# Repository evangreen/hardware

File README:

USBtiny
=======

USBtiny is a software implementation of the USB low-speed protocol for
the Atmel ATtiny microcontrollers. Of course, it will also work on the
ATmega series. The software is written for an AVR clocked at 12 MHz.
At this frequency, each bit on the USB bus takes 8 clock cycles, and
with a lot of trickery, it is possible to decode and encode the USB
waveforms by software. The USB driver needs between 1300 and 1400
bytes of flash space (excluding the optional identification strings),
depending on the configuration and compiler version, and 46 bytes RAM
(excluding stack space). The C interface consists of 3 to 5 functions,
depending on the configuration.

Implementation
==============

USB uses two differential data signals, D+ and D-, which are normally
complementary. However, the end of a packet is signalled by pulling
both signals low. Data is not transmitted directly on the USB bus, it
is NRZI encoded first. This means that a "0" bit is encoded as a bit
change, and a "1" bit is encoded as no bit change. After 6 "1" bits,
"bit stuffing" takes place to force a change on the USB signal lines.

The software is interrupt driven: the start of a USB packet triggers
an interrupt. The interrupt handler synchronizes with the sync byte,
removes the NRZI encoding and bit stuffing, and stores the packed in
one of the two RAM buffers. Two buffers are used so that the next
packet can be received while the current one is being processed.
Depending on the packet type, a reply packed may be sent back
immediately in the interrupt handler.

The rest of the USB driver is written in C. A usb_poll() function
must to be called periodically to poll for incoming packets. Only a
single endpoint is supported at the moment. Standard control requests
are directly handled by the USB driver. Other SETUP requests are
forwarded to a user-supplied function usb_setup(). Support for large
replies and OUT control requests is optional, see usbtiny.h.

To use the USB driver in your own application, you need to configure
the macros in usbtiny.h, and provide a function usb_setup() to handle
SETUP control packets. Optionally, you need to provide the functions
usb_in() and usb_out(). Your code needs to call the initialization
function usb_init() at program startup, and usb_poll() at regular
intervals. The AVR device type and the upload command should be
configured at the top of the Makefile.

Other USB projects
==================

This software was inspired by two similar USB projects for the AVR:

  http://www.cesko.host.sk/IgorPlugUSB/IgorPlug-USB%20(AVR)_eng.htm
  http://www.obdev.at/products/avrusb/index.html

My version has the advantage that you have more freedom over which I/O
pins to use for the D+ and D- USB signals. You don't need to use bit 0
for the D+ signal. The only restriction is that both signals should be
on the same I/O port. When you select a pin for D+ that can also
generate an interrupt, only two I/O pins are required. The pin-change
interrupt is deliberately not used, so that it remains available for
other uses.

Another improvement is that the CRC calculation is faster, because it
uses a lookup table. A bit-wise calculation turned out to be too slow
for the USB controller in my laptop. For instance, the obdev code
worked fine on my desktop computer, but not on my laptop.

Apart from these advantages, I think that my code is more readable and
easier to configure, but that impression may be caused by a mild form
of the NIH syndrome that I'm suffering from. In any case, I learned a
lot about the USB protocol, and writing the interrupt handler was a
nice puzzle.

Hardware
========

The AVR must be clocked with an external 12 MHz crystal. For an
ATtiny2313, this means that the low fuse byte must be reprogrammed,
for instance to 0xff. I also recommend to enable the BOD circuit,
when available. For the ATtiny2313, this means programming the high
fuse byte to 0xdb (BOD level is 2.7V).

The USB data signals are specified at 3.3V. The easiest way to
accomplish this is to use a 3.3V power supply for the AVR. However,
driving the USB signals with 5V seems to work as well in most cases,
which may be more convenient when you need to interface to 5V
peripherals. According to the USB specification, a device should not
be damaged by 5V signals. I've been running the AVR and USB bus at 5V,
and haven't encounter any problems so far, but I have some reports
of Viao laptops that do not work with 5V signals. In that case, you
can reduce the voltage of the USB data signals by adding 3V6 zener
diodes from the data signals to ground.

USBtiny SPI converter
=====================

My first USBtiny application is a USB to SPI (Serial Programming
Interface) converter. The SPI signals are connected to a female DB-25
connecter, so that the converter can be plugged onto my AVR parallel
port programmer. Because the most important parallel port signals are
connected to the DB-25 connecter, the same hardware (with different
firmware) could be used to control other parallel port devices. That
is also the reason why I connected the ACK signal to the INT1 pin.
I didn't bother to put capacitors on the crystal, but they are
recommended for reliable operation. The software, the schematic and
a Python test script can be found in the "spi" subdirectory.

The circuit may be powered via the diode at pin 14 of the DB-25
connector to enable reprograming the ATtiny2313 in-system. This
requires an adaptor cable between another SPI programmer and a DB-25
male connector with the following connections:

  SPI  DB25
  ---  ----
  GND    25
  VCC    14
  RESET  13
  SCK     9
  MISO    8
  MOSI    7

Bit-banging the SPI signals via USB turned out to be very slow. To get
reasonable programming speeds, I've moved the SPI algorithm into the
AVR. This means that you can send a 32-bit SPI command in a single USB
packet. In addition, you can read or write up to 255 bytes from/to
flash or EEPROM in a single control transfer.

The subdirectory "patches" contains a patch for avrdude-5.1 that adds
support for controlling this SPI converter. The programmer name is
"usbtiny". You can use the -B option or the "sck" command to specify
the minimum SCK period in microseconds (range: 1..250, default: 10).

USBtiny LIRC compatible IR receiver and LCD controller
======================================================

A second USBtiny application is a receiver for infrared remote
controls that can be used with the LIRC package (http://www.lirc.org/).
The firmware stores the mark/space timings from a TSOP1738 IR decoder
in a buffer that is polled by a LIRC device driver. As a visual
feedback, a LED is flashed when a signal is being received. As an
additional (optional) feature, a 2x16 LCD display is attached to PORTB.
You can control the display via the USB bus. The software, the schematic
and a Python test script can be found in the "ir" subdirectory.
A pull-down resistor at PB3 prevents a hang in the LCD initialization
code when no LCD is attached to PORTB. You can disable the LCD code by
setting the LCD_PRESENT macro in main.c to 0.

I adopted the "IgorPlug-USB" protocol, so that the existing LIRC
device driver "igorplugusb" could be used without modifications.
Nevertheless, a patch for lirc-0.8.0 is included in the "patches"
subdirectory, with the following modifications:
1) An increase of the sample rate from 10 to 100 times per second.
   This is not required, but improves the responsiveness and repeat
   behavior for some remote controls.
2) A fix from Reinhard Max to get correct gap timings.
3) A compilation fix for the latest 2.6 Linux kernels.

Tools
=====

The software was developed on a Linux system. In addition to standard
tools like GNU make, you need the AVR versions of gcc, binutils and
glibc to build the code: On a Debian/Ubuntu system, you can apt-get
the following packages:

  gcc-avr
  binutils-avr
  avr-libc

To upload the code to an AVR, I use avrdude with a parallel port
programmer.

I initially used gcc-3.4.3 with the -Os option, which generates
reasonable compact code. Unfortunately, newer versions like gcc-4.1.0
generate about 10% more code, and as a result, the application code
did not fit in 2K anymore. To make it fit, I had to remove the optional
vendor and device strings, by undefining the USBTINY_VENDOR_NAME and
USBTINY_DEVICE_NAME macros.

The schematics were created with gschem, which is part of the gEDA
package. The conversion to Postscript is done with a script that
invokes gschem non-interactively.

The "util" and application code subdirectories each contain their own
Makefile. In addition, there is a global Makefile that recursively
invokes all other Makefiles.

Host software
=============

The subdirectory "utils" contains a Python module "usbtiny.py" that
defines a class USBtiny that can be used to communicate with the
USBtiny firmware. This class is used by the test scripts.

The usbtiny.py module uses a Python wrapper around libusb that is
generated by "swig". Type "make" to build the wrapper. Of course, you
need to have swig, libusb and libusb-dev installed on your system.

Libusb needs appropriate permissions to open a USB device. This means
that you either have to run the scripts as "root", or you should
configure the hotplug or udev system to relax the permissions of the
device file created under /proc/bus/usb/ when the device is plugged
in. With udev, you can change the permissions by adding a rule like

  SUBSYSTEM=="usb_device", MODE="0666"

to the udev rules in /etc/udev/rules.d/

License
=======

The USBtiny software is licensed under the terms of the GNU General
Public License as published by the Free Software Foundation, either
version 2 of the license, or (at your option) any later version. A
copy of the GPL version 2 license can be found in the file COPYING.

Author & website
================

Dick Streefland <dick@streefland.net>

http://www.google.com/search?btnI&q=webtag_net_streefland_avr_usbtiny

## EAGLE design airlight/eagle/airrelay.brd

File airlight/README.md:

# Airlight

Airlight was a set of two hardware boards I started in 2013 in order to control the traffic lights I've collected in my house. It was also my first foray into the world of Wireless with the RFM22B boards.

### Design

The system consists of two components: a master board and several identical relay boards (one in each traffic light).

The master board is the brains behind the system. It contains the traffic controller logic, and sends out wireless commands to the relay boards in the traffic lights. The controller logic is an 8-phase semi-actuated traffic controller based on my previous work in college studying an old Crouse Hinds DM-800 controller. There are only enough LEDs to display 4 phases at once, but the controller logic can technically run 8 phases plus 4 overlap lights. This is equivalent to a 4 way intersection with protected lefts and protected rights in each direction. The traffic controller part also compiles for Windows so that I can test the traffic control sequencing without burning new firmware.

The relay boards are nearly stateless. They have a phase ID and pedestrian boolean burned uniquely into the firmware of each board so that each light knows which phase to respond to. They listen for wireless commands and respond appropriately. I also programmed in an RSSI response mode in case I needed to debug signal quality issues.

The relay board receives commands via the RFM22B wireless board into an ATMega168 MCU. It listens to incoming wireless messages corresponding to its phase and ped ID, and updates its 3 output pins (red, yellow, and green). The output pins are connected via optoisolators to triacs, which can flip 120VAC line voltage on or off.

### Results

Overall the project went very well. I was very pleased with the signal strength of the RFM22B boards. Reception was great anywhere in my admittedly tiny apartment, even though the relay boards were buried inside metal traffic lights. There are a couple of board errata, which were easy enough to fix and should be documented.

One aspect that I'm less than pleased about is the sharing of the SPI bus between the RFM22B and the LEDs on the master board. The RFM22B is very slow to respond, and hogs the bus for long delay periods, meaning every time a wireless command is sent there is visible flickering in the LEDs. If I had known the RFM22B was going to be a so slow I would have wired the LEDs separately, or maybe used something like an HT16K33 to drive the LEDs.

### Pictures
Some photos of the lights in my apartment

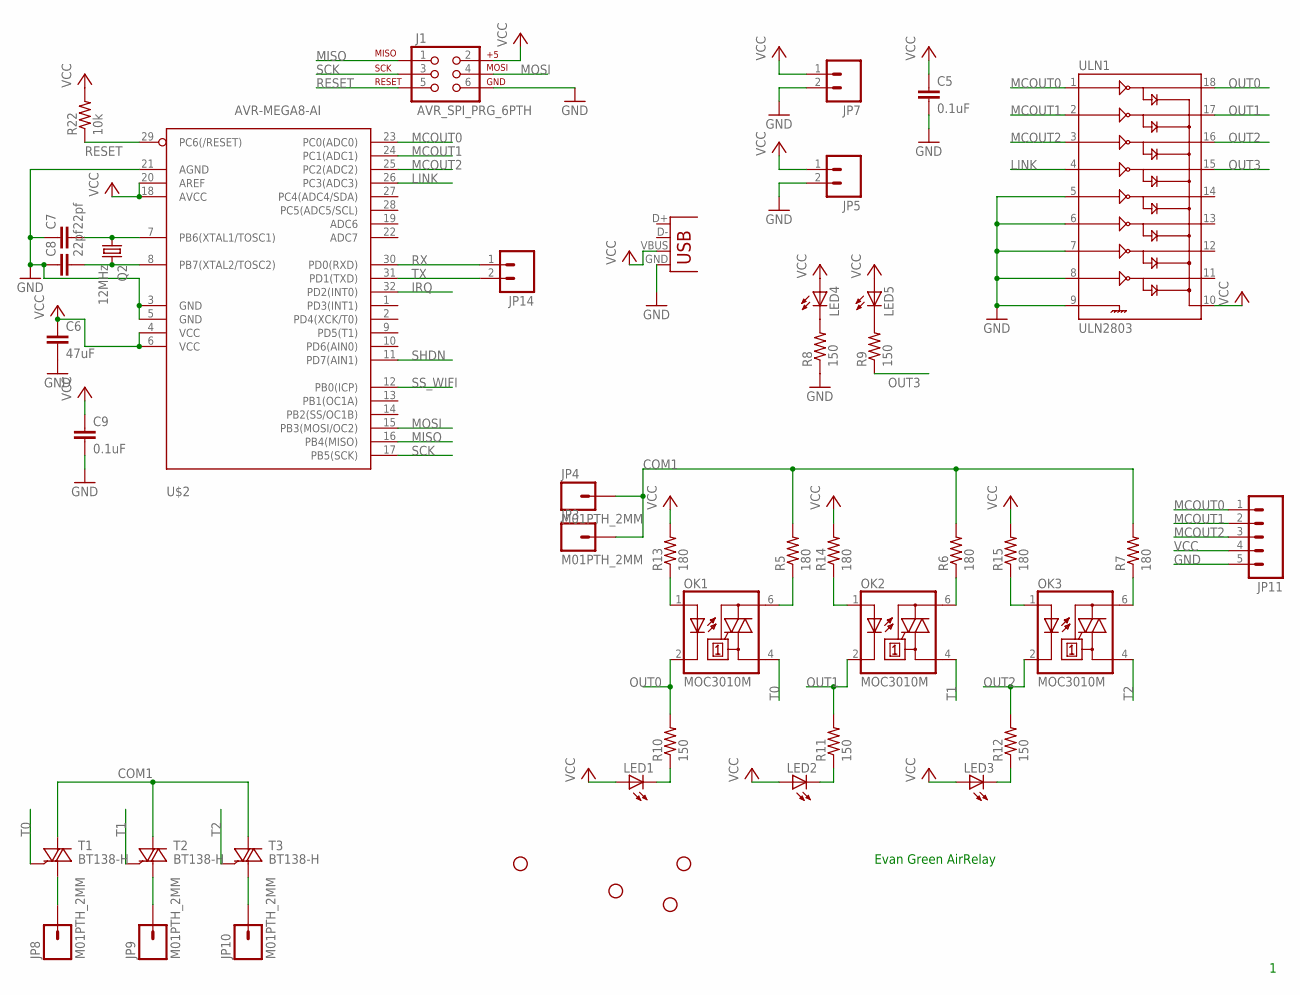
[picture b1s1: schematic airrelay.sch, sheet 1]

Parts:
C5, C9: 0.1uF; 0402-CAP
C6: 47uF; 1210
C7, C8: 22pf; 0402-CAP
J1: AVR_SPI_PRG_6PTH; 2X3
JP2, JP6, JP12, JP13: STAND-OFF
JP3, JP4, JP8, JP9, JP10: M01PTH_2MM; 1X01_2MM
JP5, JP7, JP14: M02PTH; 1X02
JP11: M05PTH; 1X05
LED1, LED2, LED3: LED5MM
LED4, LED5: LED3MM
OK1, OK2, OK3: MOC3010M; DIL06
Q2: 12MHz; TC38H
R5, R6, R7: 180; AXIAL-0.4
R8, R9, R10, R11, R12: 150; 0402-RES
R13, R14, R15: 180; 0402-RES
R22: 10k; 0402-RES
T1, T2, T3: BT138-H; TO220BH
U$2: AVR-MEGA8-AI; TQFP32-08
ULN1: ULN2803; SO18L
X1: USBSMD; USB-MINIB

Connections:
COM1: JP3.1, JP4.1, R5.P$2 (2), R6.P$2 (2), R7.P$2 (2), T1.T2 (A2), T2.T2 (A2), T3.T2 (A2)
GND: C5.2, C6.2, C7.1, C8.1, C9.2, J1.6, JP5.2, JP7.2, JP11.5, R8.1, U$2.3 (GND), U$2.5 (GND), U$2.21 (AGND), ULN1.5, ULN1.6, ULN1.7, ULN1.8, ULN1.9, X1.GND; also elsewhere on the board
IRQ: U$2.32 (PD2(INT0)); also elsewhere on the board
LINK: U$2.26 (PC3(ADC3)), ULN1.4
MCOUT0: JP11.1, U$2.23 (PC0(ADC0)), ULN1.1
MCOUT1: JP11.2, U$2.24 (PC1(ADC1)), ULN1.2
MCOUT2: JP11.3, U$2.25 (PC2(ADC2)), ULN1.3
MISO: J1.1, U$2.16 (PB4(MISO))
MOSI: J1.4, U$2.15 (PB3(MOSI/OC2)); also elsewhere on the board
unnamed: OK1.1 (A), R13.1
unnamed: OK2.1 (A), R14.1
unnamed: OK3.1 (A), R15.1
unnamed: LED4.K (C), R8.2
unnamed: LED5.K (C), R9.2
unnamed: LED3.K (C), R12.1
unnamed: OK1.6 (A2), R5.P$1 (1)
unnamed: OK2.6 (A2), R6.P$1 (1)
unnamed: OK3.6 (A2), R7.P$1 (1)
unnamed: LED2.K (C), R11.1
unnamed: LED1.K (C), R10.1
unnamed: C7.2, Q2.1, U$2.7 (PB6(XTAL1/TOSC1))
unnamed: JP8.1, T1.T1 (A1)
unnamed: JP9.1, T2.T1 (A1)
unnamed: JP10.1, T3.T1 (A1)
unnamed: C8.2, Q2.2, U$2.8 (PB7(XTAL2/TOSC2))
OUT0: OK1.2 (C), R10.2, ULN1.18
OUT1: OK2.2 (C), R11.2, ULN1.17
OUT2: OK3.2 (C), R12.2, ULN1.16
OUT3: R9.1, ULN1.15
RESET: J1.5, R22.1, U$2.29 (PC6(/RESET))
RX: JP14.1, U$2.30 (PD0(RXD))
SCK: J1.3, U$2.17 (PB5(SCK)); also elsewhere on the board
SHDN: U$2.11 (PD7(AIN1)); also elsewhere on the board
SS_WIFI: U$2.12 (PB0(ICP)); also elsewhere on the board
T0: OK1.4 (A1), T1.G
T1: OK2.4 (A1), T2.G
T2: OK3.4 (A1), T3.G
TX: JP14.2, U$2.31 (PD1(TXD))
VCC: C5.1, C6.1, C9.1, J1.2, JP5.1, JP7.1, JP11.4, LED1.A, LED2.A, LED3.A, LED4.A, LED5.A, R13.2, R14.2, R15.2, R22.2, U$2.4 (VCC), U$2.6 (VCC), U$2.18 (AVCC), U$2.20 (AREF), ULN1.10, X1.VBUS

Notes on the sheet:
Evan Green AirRelay

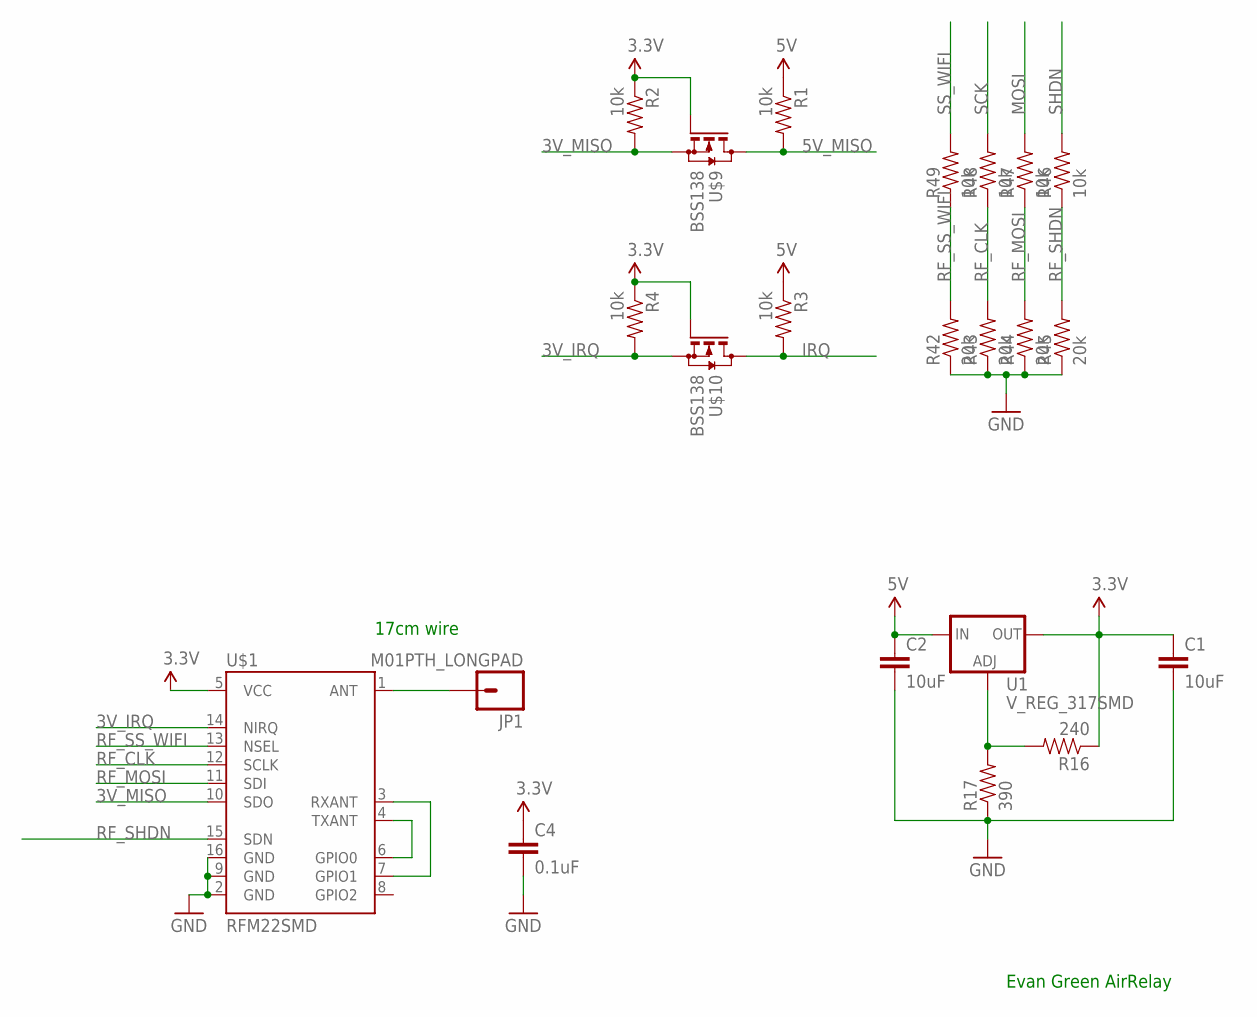
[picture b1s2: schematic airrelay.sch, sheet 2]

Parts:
C1, C2: 10uF; 0805
C4: 0.1uF; 0402-CAP
JP1: M01PTH_LONGPAD; 1X01_LONGPAD
R1, R2, R3, R4, R46, R47, R48, R49: 10k; 0402-RES
R16: 240; 0402-RES
R17: 390; 0402-RES
R42, R43, R44, R45: 20k; 0402-RES
U1: V_REG_317SMD; SOT223
U$1: RFM22SMD; RFM22-XXX-S2
U$9, U$10: BSS138; SOT-323

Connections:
3.3V: C1.1, C4.1, R2.1, R4.1, R16.1, U1.2 (OUT), U$1.5 (VCC), U$9.1 (G), U$10.1 (G)
3V_IRQ: R4.2, U$1.14 (NIRQ), U$10.2 (S)
3V_MISO: R2.2, U$1.10 (SDO), U$9.2 (S)
5V: C2.1, R1.1, R3.1, U1.3 (IN)
5V_MISO: R1.2, U$9.3 (D)
GND: C1.2, C2.2, C4.2, R17.1, R42.1, R43.1, R44.1, R45.1, U$1.2 (GND), U$1.9 (GND), U$1.16 (GND); also elsewhere on the board
IRQ: R3.2, U$10.3 (D); also elsewhere on the board
MOSI: R47.2; also elsewhere on the board
unnamed: R16.2, R17.2, U1.1 (ADJ)
unnamed: U$1.4 (TXANT), U$1.6 (GPIO0)
unnamed: JP1.1, U$1.1 (ANT)
unnamed: U$1.3 (RXANT), U$1.7 (GPIO1)
RF_CLK: R43.2, R48.1, U$1.12 (SCLK)
RF_MOSI: R44.2, R47.1, U$1.11 (SDI)
RF_SHDN: R45.2, R46.1, U$1.15 (SDN)
RF_SS_WIFI: R42.2, R49.1, U$1.13 (NSEL)
SCK: R48.2; also elsewhere on the board
SHDN: R46.2; also elsewhere on the board
SS_WIFI: R49.2; also elsewhere on the board

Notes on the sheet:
Evan Green AirRelay
17cm wire

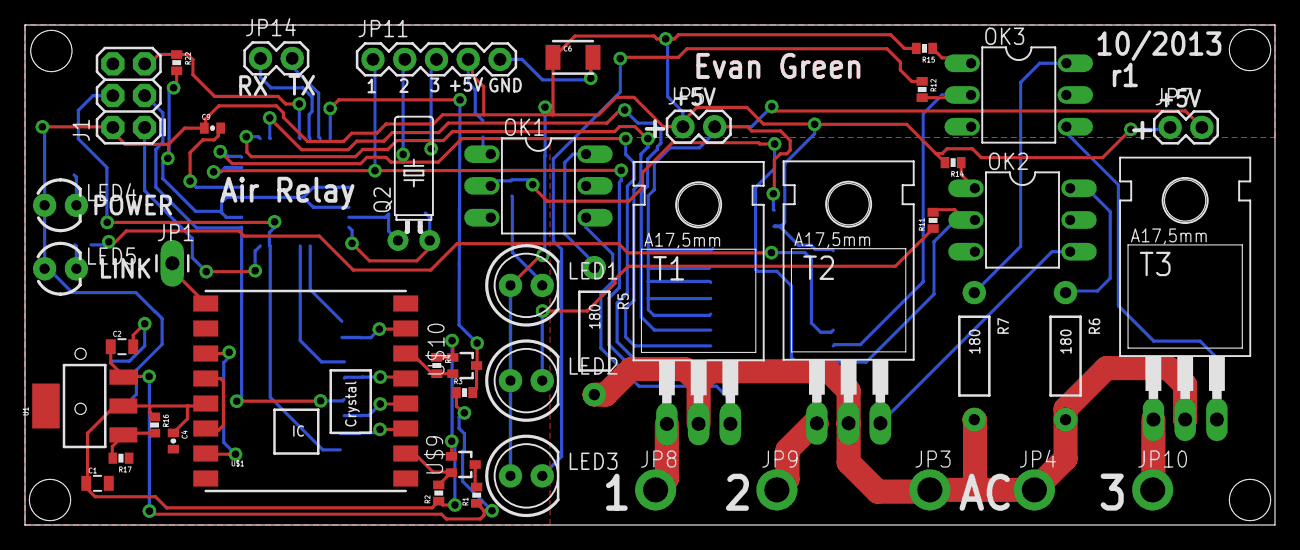
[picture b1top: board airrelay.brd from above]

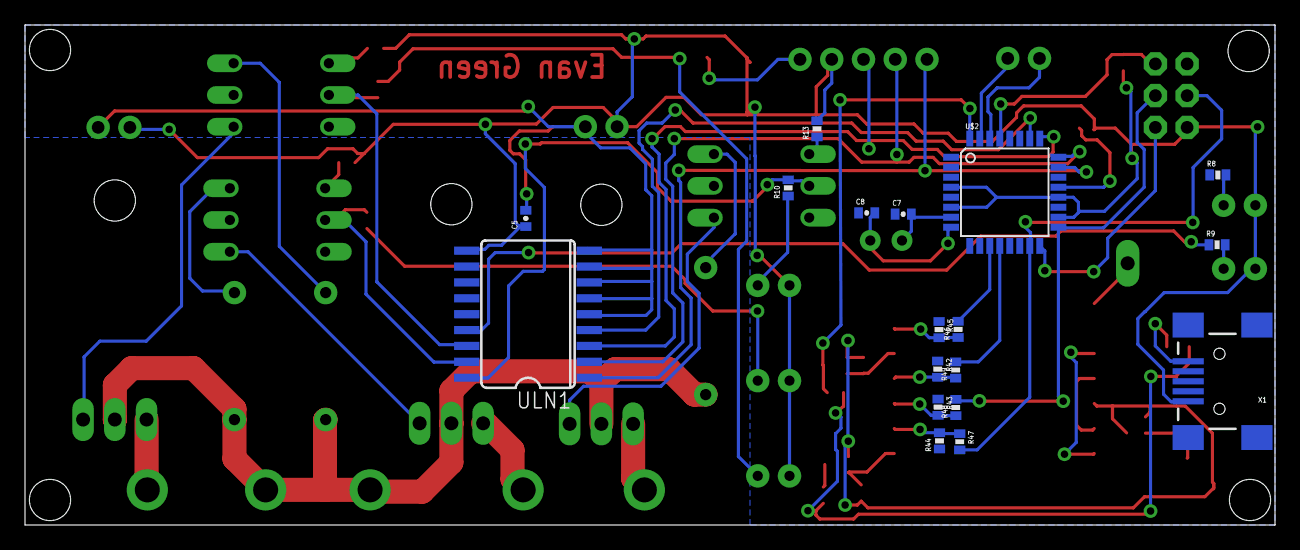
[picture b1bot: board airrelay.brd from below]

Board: 2 copper layers, 100.0 x 40.0 mm, 68 parts (18 on the bottom side), 52 nets.

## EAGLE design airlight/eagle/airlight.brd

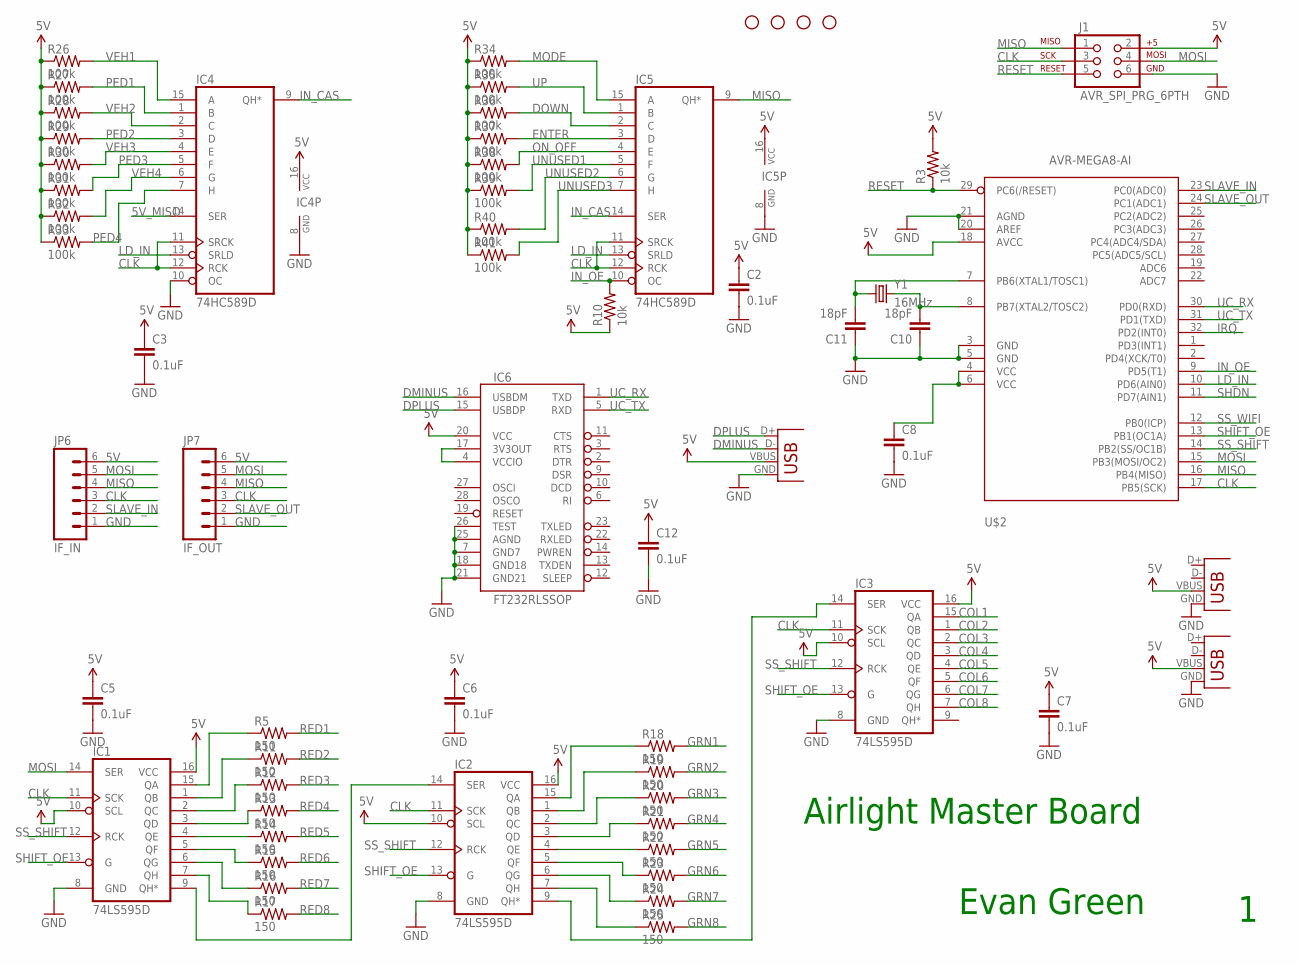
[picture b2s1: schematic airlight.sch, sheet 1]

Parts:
C2, C3, C5, C6, C7, C8, C12: 0.1uF; 0402-CAP
C10, C11: 18pF; 0402-CAP
IC1, IC2, IC3: 74LS595D; SO16
IC4, IC5: 74HC589D; SO16
IC6: FT232RLSSOP; SSOP28DB
J1: AVR_SPI_PRG_6PTH; 2X3
JP2, JP3, JP4, JP5: STAND-OFF
JP6: IF_IN; 1X06
JP7: IF_OUT; 1X06
R3, R10: 10k; 0402-RES
R5, R11, R12, R13, R14, R15, R16, R17, R18, R19, R20, R21, R22, R23, R24, R25: 150; 0402-RES
R26, R27, R28, R29, R30, R31, R32, R33, R34, R35, R36, R37, R38, R39, R40, R41: 100k; 0402-RES
U$2: AVR-MEGA8-AI; TQFP32-08
X1, X2, X3: USBSMD; USB-MINIB
Y1: 16MHz; HC49US

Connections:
5V: C2.1, C3.1, C5.1, C6.1, C7.1, C12.1, IC1.10 (SCL), IC1.16 (VCC), IC2.10 (SCL), IC2.16 (VCC), IC3.10 (SCL), IC3.16 (VCC), IC4.16 (VCC), IC5.16 (VCC), IC6.20 (VCC), J1.2, JP6.6, JP7.6, R3.2, R10.1, R26.1, R27.1, R28.1, R29.1, R30.1, R31.1, R32.1, R33.1, R34.1, R35.1, R36.1, R37.1, R38.1, R39.1, R40.1, R41.1, U$2.18 (AVCC), X1.VBUS, X2.VBUS, X3.VBUS; also elsewhere on the board
5V_MISO: IC4.14 (SER); also elsewhere on the board
CLK: IC1.11 (SCK), IC2.11 (SCK), IC3.11 (SCK), IC4.11 (SRCK), IC4.12 (RCK), IC5.11 (SRCK), IC5.12 (RCK), J1.3, JP6.3, JP7.3, U$2.17 (PB5(SCK)); also elsewhere on the board
COL1: IC3.15 (QA); also elsewhere on the board
COL2: IC3.1 (QB); also elsewhere on the board
COL3: IC3.2 (QC); also elsewhere on the board
COL4: IC3.3 (QD); also elsewhere on the board
COL5: IC3.4 (QE); also elsewhere on the board
COL6: IC3.5 (QF); also elsewhere on the board
COL7: IC3.6 (QG); also elsewhere on the board
COL8: IC3.7 (QH); also elsewhere on the board
DMINUS: IC6.16 (USBDM), X1.D-
DOWN: IC5.2 (C), R36.2; also elsewhere on the board
DPLUS: IC6.15 (USBDP), X1.D+
ENTER: IC5.3 (D), R37.2; also elsewhere on the board
GND: C2.2, C3.2, C5.2, C6.2, C7.2, C8.2, C10.1, C11.1, C12.2, IC1.8 (GND), IC2.8 (GND), IC3.8 (GND), IC4.8 (GND), IC4.10 (OC), IC5.8 (GND), IC6.7 (GND7), IC6.18 (GND18), IC6.21 (GND21), IC6.25 (AGND), IC6.26 (TEST), J1.6, JP6.1, JP7.1, U$2.3 (GND), U$2.5 (GND), U$2.20 (AREF), U$2.21 (AGND), X1.GND, X2.GND, X3.GND; also elsewhere on the board
GRN1: R18.2; also elsewhere on the board
GRN2: R19.2; also elsewhere on the board
GRN3: R20.2; also elsewhere on the board
GRN4: R21.2; also elsewhere on the board
GRN5: R22.2; also elsewhere on the board
GRN6: R23.2; also elsewhere on the board
GRN7: R24.2; also elsewhere on the board
GRN8: R25.2; also elsewhere on the board
IN_CAS: IC4.9 (QH*), IC5.14 (SER)
IN_OE: IC5.10 (OC), R10.2, U$2.9 (PD5(T1))
IRQ: U$2.32 (PD2(INT0)); also elsewhere on the board
LD_IN: IC4.13 (SRLD), IC5.13 (SRLD), U$2.10 (PD6(AIN0))
MISO: IC5.9 (QH*), J1.1, JP6.4, JP7.4, U$2.16 (PB4(MISO))
MODE: IC5.15 (A), R34.2; also elsewhere on the board
MOSI: IC1.14 (SER), J1.4, JP6.5, JP7.5, U$2.15 (PB3(MOSI/OC2)); also elsewhere on the board
unnamed: IC1.15 (QA), R5.1
unnamed: IC1.1 (QB), R11.1
unnamed: IC1.2 (QC), R12.1
unnamed: IC1.3 (QD), R13.1
unnamed: IC1.4 (QE), R14.1
unnamed: IC1.5 (QF), R15.1
unnamed: IC1.6 (QG), R16.1
unnamed: IC1.7 (QH), R17.1
unnamed: C11.2, U$2.7 (PB6(XTAL1/TOSC1)), Y1.1
unnamed: C10.2, U$2.8 (PB7(XTAL2/TOSC2)), Y1.2
unnamed: IC2.15 (QA), R18.1
unnamed: IC2.1 (QB), R19.1
unnamed: IC2.2 (QC), R20.1
unnamed: IC2.3 (QD), R21.1
unnamed: IC2.4 (QE), R22.1
unnamed: IC2.5 (QF), R23.1
unnamed: IC2.6 (QG), R24.1
unnamed: IC2.7 (QH), R25.1
unnamed: IC6.4 (VCCIO), IC6.17 (3V3OUT)
unnamed: IC2.9 (QH*), IC3.14 (SER)
unnamed: C8.1, U$2.4 (VCC), U$2.6 (VCC)
unnamed: IC1.9 (QH*), IC2.14 (SER)
ON_OFF: IC5.4 (E), R38.2; also elsewhere on the board
PED1: IC4.1 (B), R27.2; also elsewhere on the board
PED2: IC4.3 (D), R29.2; also elsewhere on the board
PED3: IC4.5 (F), R31.2; also elsewhere on the board
PED4: IC4.7 (H), R33.2; also elsewhere on the board
RED1: R5.2; also elsewhere on the board
RED2: R11.2; also elsewhere on the board
RED3: R12.2; also elsewhere on the board
RED4: R13.2; also elsewhere on the board
RED5: R14.2; also elsewhere on the board
RED6: R15.2; also elsewhere on the board
RED7: R16.2; also elsewhere on the board
RED8: R17.2; also elsewhere on the board
RESET: J1.5, R3.1, U$2.29 (PC6(/RESET))
SHDN: U$2.11 (PD7(AIN1)); also elsewhere on the board
SHIFT_OE: IC1.13 (G), IC2.13 (G), IC3.13 (G), U$2.13 (PB1(OC1A))
SLAVE_IN: JP6.2, U$2.23 (PC0(ADC0))
SLAVE_OUT: JP7.2, U$2.24 (PC1(ADC1))
SS_SHIFT: IC1.12 (RCK), IC2.12 (RCK), IC3.12 (RCK), U$2.14 (PB2(SS/OC1B))
SS_WIFI: U$2.12 (PB0(ICP)); also elsewhere on the board
UC_RX: IC6.1 (TXD), U$2.30 (PD0(RXD))
UC_TX: IC6.5 (RXD), U$2.31 (PD1(TXD))
UNUSED1: IC5.5 (F), R39.2
UNUSED2: IC5.6 (G), R40.2
UNUSED3: IC5.7 (H), R41.2
UP: IC5.1 (B), R35.2; also elsewhere on the board
VEH1: IC4.15 (A), R26.2; also elsewhere on the board
VEH2: IC4.2 (C), R28.2; also elsewhere on the board
VEH3: IC4.4 (E), R30.2; also elsewhere on the board
VEH4: IC4.6 (G), R32.2; also elsewhere on the board

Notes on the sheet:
Airlight Master Board
Evan Green

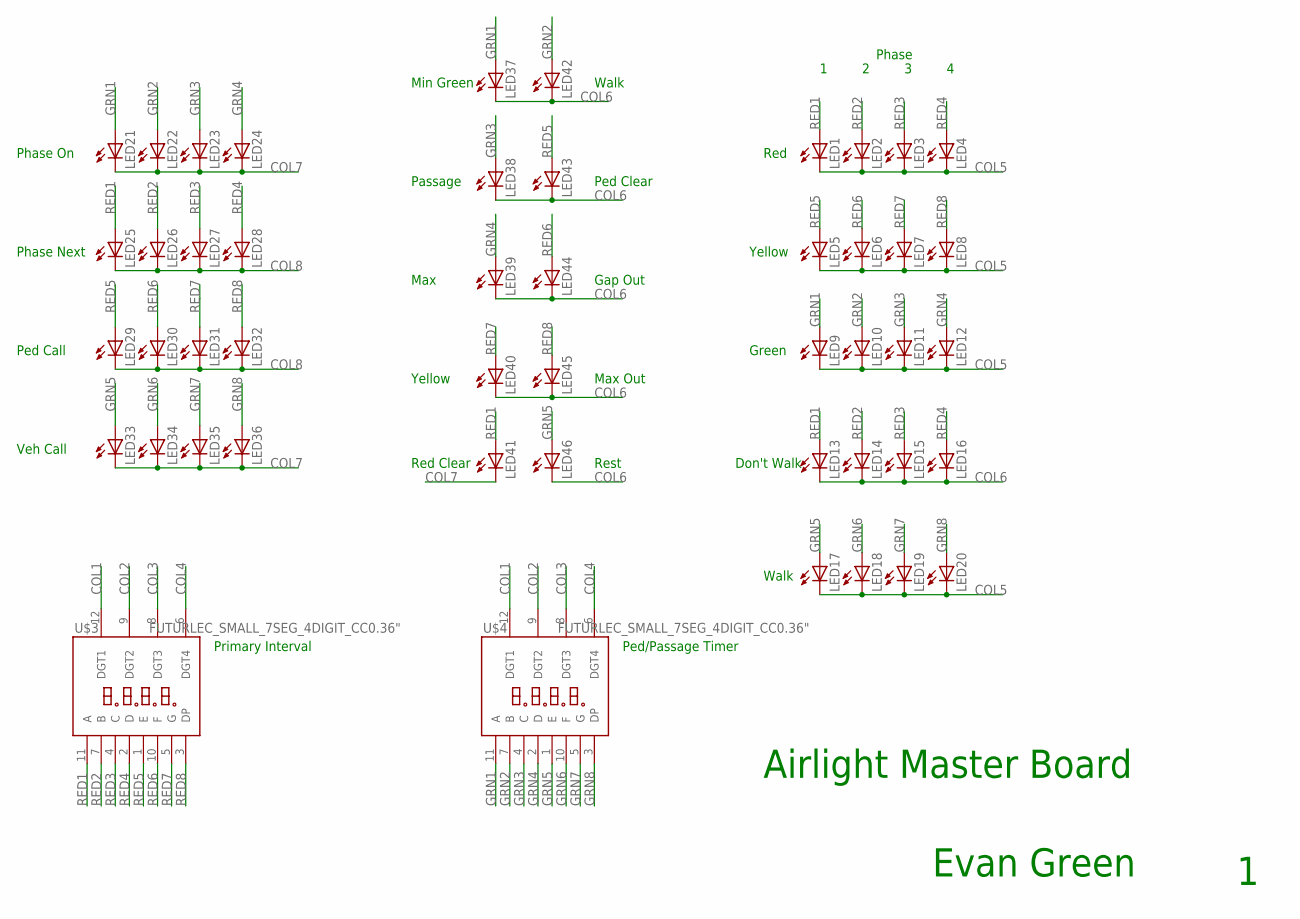
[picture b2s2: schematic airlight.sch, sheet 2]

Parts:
LED1, LED2, LED3, LED4, LED5, LED6, LED7, LED8, LED9, LED10, LED11, LED12, LED13, LED14, LED15, LED16, LED17, LED18, LED19, LED20, LED21, LED22, LED23, LED24, LED25, LED26, LED27, LED28, LED29, LED30, LED31, LED32, LED33, LED34, LED35, LED36, LED37, LED38, LED39, LED40, LED41, LED42, LED43, LED44, LED45, LED46: LED5MM
U$3, U$4: FUTURLEC_SMALL_7SEG_4DIGIT_CC0.36"; FUTURLEC_SMALL_7SEG_4DIGIT_CC

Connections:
COL1: U$3.12 (DGT1), U$4.12 (DGT1); also elsewhere on the board
COL2: U$3.9 (DGT2), U$4.9 (DGT2); also elsewhere on the board
COL3: U$3.8 (DGT3), U$4.8 (DGT3); also elsewhere on the board
COL4: U$3.6 (DGT4), U$4.6 (DGT4); also elsewhere on the board
COL5: LED1.K (C), LED2.K (C), LED3.K (C), LED4.K (C), LED5.K (C), LED6.K (C), LED7.K (C), LED8.K (C), LED9.K (C), LED10.K (C), LED11.K (C), LED12.K (C), LED17.K (C), LED18.K (C), LED19.K (C), LED20.K (C); also elsewhere on the board
COL6: LED13.K (C), LED14.K (C), LED15.K (C), LED16.K (C), LED37.K (C), LED38.K (C), LED39.K (C), LED40.K (C), LED42.K (C), LED43.K (C), LED44.K (C), LED45.K (C), LED46.K (C); also elsewhere on the board
COL7: LED21.K (C), LED22.K (C), LED23.K (C), LED24.K (C), LED33.K (C), LED34.K (C), LED35.K (C), LED36.K (C), LED41.K (C); also elsewhere on the board
COL8: LED25.K (C), LED26.K (C), LED27.K (C), LED28.K (C), LED29.K (C), LED30.K (C), LED31.K (C), LED32.K (C); also elsewhere on the board
GRN1: LED9.A, LED21.A, LED37.A, U$4.11 (A); also elsewhere on the board
GRN2: LED10.A, LED22.A, LED42.A, U$4.7 (B); also elsewhere on the board
GRN3: LED11.A, LED23.A, LED38.A, U$4.4 (C); also elsewhere on the board
GRN4: LED12.A, LED24.A, LED39.A, U$4.2 (D); also elsewhere on the board
GRN5: LED17.A, LED33.A, LED46.A, U$4.1 (E); also elsewhere on the board
GRN6: LED18.A, LED34.A, U$4.10 (F); also elsewhere on the board
GRN7: LED19.A, LED35.A, U$4.5 (G); also elsewhere on the board
GRN8: LED20.A, LED36.A, U$4.3 (DP); also elsewhere on the board
RED1: LED1.A, LED13.A, LED25.A, LED41.A, U$3.11 (A); also elsewhere on the board
RED2: LED2.A, LED14.A, LED26.A, U$3.7 (B); also elsewhere on the board
RED3: LED3.A, LED15.A, LED27.A, U$3.4 (C); also elsewhere on the board
RED4: LED4.A, LED16.A, LED28.A, U$3.2 (D); also elsewhere on the board
RED5: LED5.A, LED29.A, LED43.A, U$3.1 (E); also elsewhere on the board
RED6: LED6.A, LED30.A, LED44.A, U$3.10 (F); also elsewhere on the board
RED7: LED7.A, LED31.A, LED40.A, U$3.5 (G); also elsewhere on the board
RED8: LED8.A, LED32.A, LED45.A, U$3.3 (DP); also elsewhere on the board

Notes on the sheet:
Red
Yellow
Green
Walk
Don't Walk
Phase On
Phase Next
Ped Call
Veh Call
Min Green
Passage
Max
Red Clear
Ped Clear
Gap Out
Max Out
Rest
Phase
Primary Interval
Ped/Passage Timer
Airlight Master Board
Evan Green

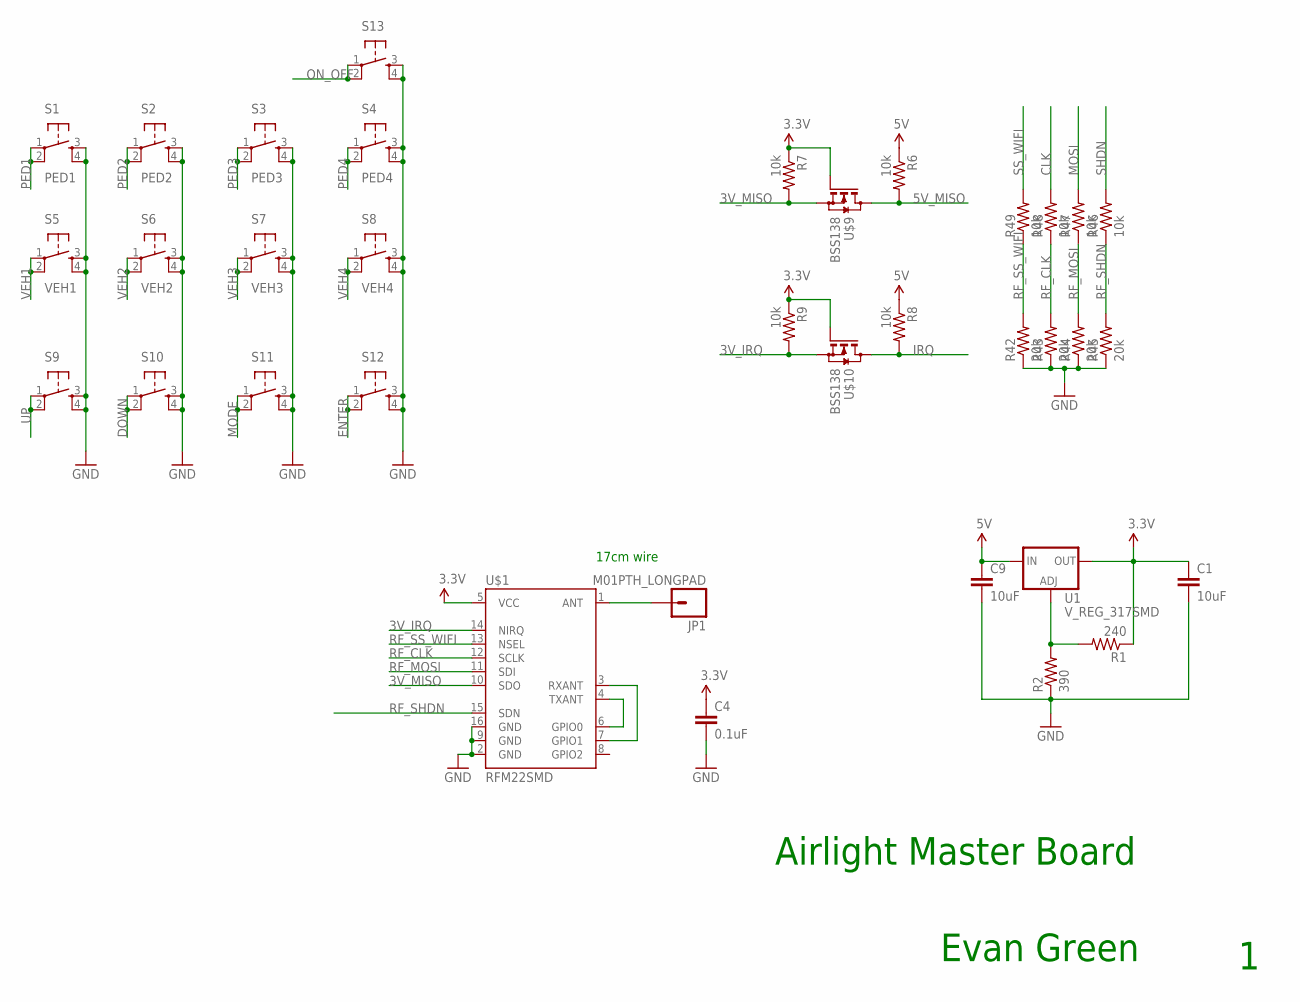
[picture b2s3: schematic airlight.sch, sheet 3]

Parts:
C1, C9: 10uF; 0805
C4: 0.1uF; 0402-CAP
JP1: M01PTH_LONGPAD; 1X01_LONGPAD
R1: 240; 0402-RES
R2: 390; 0402-RES
R6, R7, R8, R9, R46, R47, R48, R49: 10k; 0402-RES
R42, R43, R44, R45: 20k; 0402-RES
S1: PED1; TACTILE-PTH
S2: PED2; TACTILE-PTH
S3: PED3; TACTILE-PTH
S4: PED4; TACTILE-PTH
S5: VEH1; TACTILE-PTH
S6: VEH2; TACTILE-PTH
S7: VEH3; TACTILE-PTH
S8: VEH4; TACTILE-PTH
S9, S10, S11, S12, S13: TAC_SWITCHPTH; TACTILE-PTH
U1: V_REG_317SMD; SOT223
U$1: RFM22SMD; RFM22-XXX-S2
U$9, U$10: BSS138; SOT-323

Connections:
3.3V: C1.1, C4.1, R1.1, R7.1, R9.1, U1.2 (OUT), U$1.5 (VCC), U$9.1 (G), U$10.1 (G)
3V_IRQ: R9.2, U$1.14 (NIRQ), U$10.2 (S)
3V_MISO: R7.2, U$1.10 (SDO), U$9.2 (S)
5V: C9.1, R6.1, R8.1, U1.3 (IN); also elsewhere on the board
5V_MISO: R6.2, U$9.3 (D); also elsewhere on the board
CLK: R48.2; also elsewhere on the board
DOWN: S10.1, S10.2; also elsewhere on the board
ENTER: S12.1, S12.2; also elsewhere on the board
GND: C1.2, C4.2, C9.2, R2.1, R42.1, R43.1, R44.1, R45.1, S1.3, S1.4, S2.3, S2.4, S3.3, S3.4, S4.3, S4.4, S5.3, S5.4, S6.3, S6.4, S7.3, S7.4, S8.3, S8.4, S9.3, S9.4, S10.3, S10.4, S11.3, S11.4, S12.3, S12.4, S13.3, S13.4, U$1.2 (GND), U$1.9 (GND), U$1.16 (GND); also elsewhere on the board
IRQ: R8.2, U$10.3 (D); also elsewhere on the board
MODE: S11.1, S11.2; also elsewhere on the board
MOSI: R47.2; also elsewhere on the board
unnamed: U$1.4 (TXANT), U$1.6 (GPIO0)
unnamed: R1.2, R2.2, U1.1 (ADJ)
unnamed: U$1.3 (RXANT), U$1.7 (GPIO1)
unnamed: JP1.1, U$1.1 (ANT)
ON_OFF: S13.1, S13.2; also elsewhere on the board
PED1: S1.1, S1.2; also elsewhere on the board
PED2: S2.1, S2.2; also elsewhere on the board
PED3: S3.1, S3.2; also elsewhere on the board
PED4: S4.1, S4.2; also elsewhere on the board
RF_CLK: R43.2, R48.1, U$1.12 (SCLK)
RF_MOSI: R44.2, R47.1, U$1.11 (SDI)
RF_SHDN: R45.2, R46.1, U$1.15 (SDN)
RF_SS_WIFI: R42.2, R49.1, U$1.13 (NSEL)
SHDN: R46.2; also elsewhere on the board
SS_WIFI: R49.2; also elsewhere on the board
UP: S9.1, S9.2; also elsewhere on the board
VEH1: S5.1, S5.2; also elsewhere on the board
VEH2: S6.1, S6.2; also elsewhere on the board
VEH3: S7.1, S7.2; also elsewhere on the board
VEH4: S8.1, S8.2; also elsewhere on the board

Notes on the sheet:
Airlight Master Board
Evan Green
17cm wire

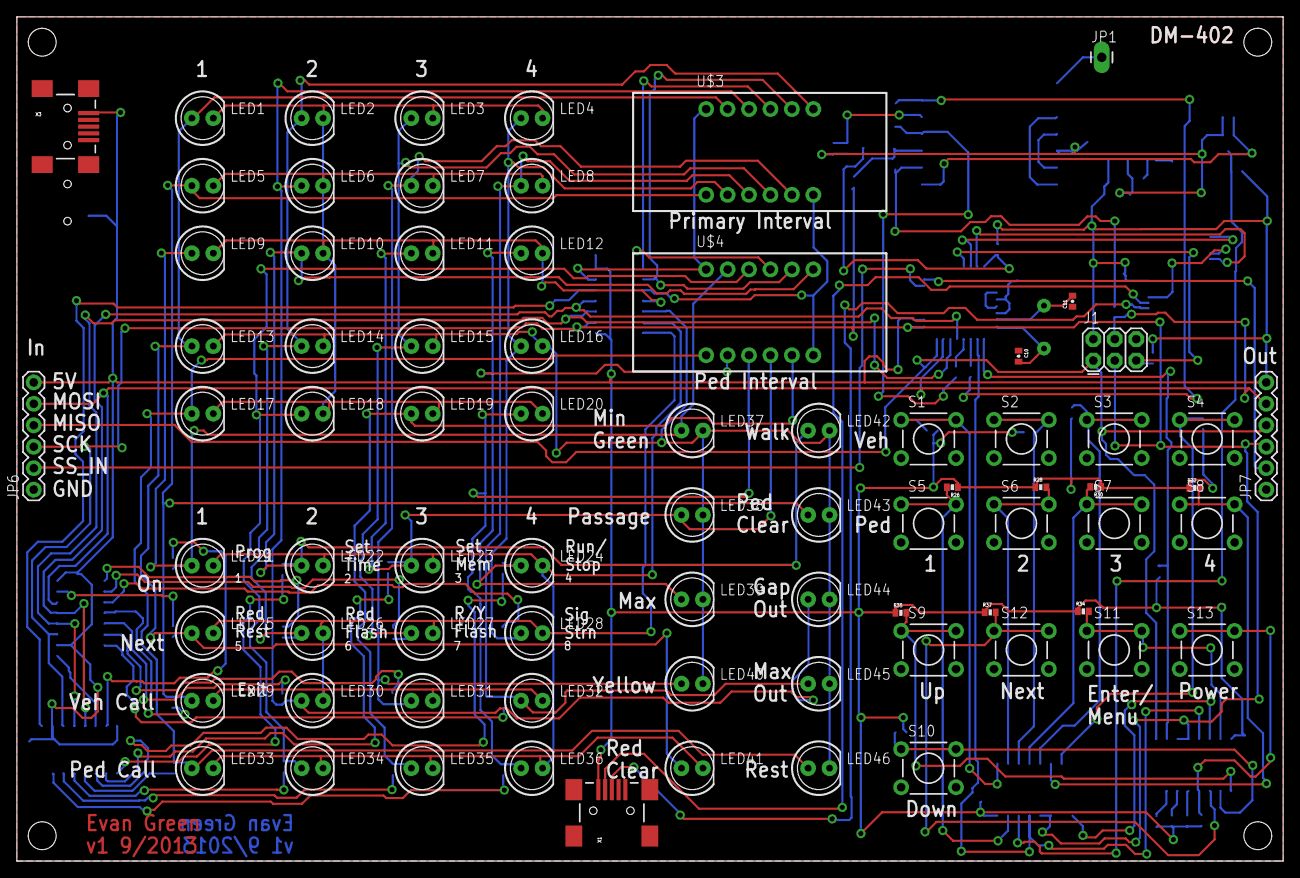
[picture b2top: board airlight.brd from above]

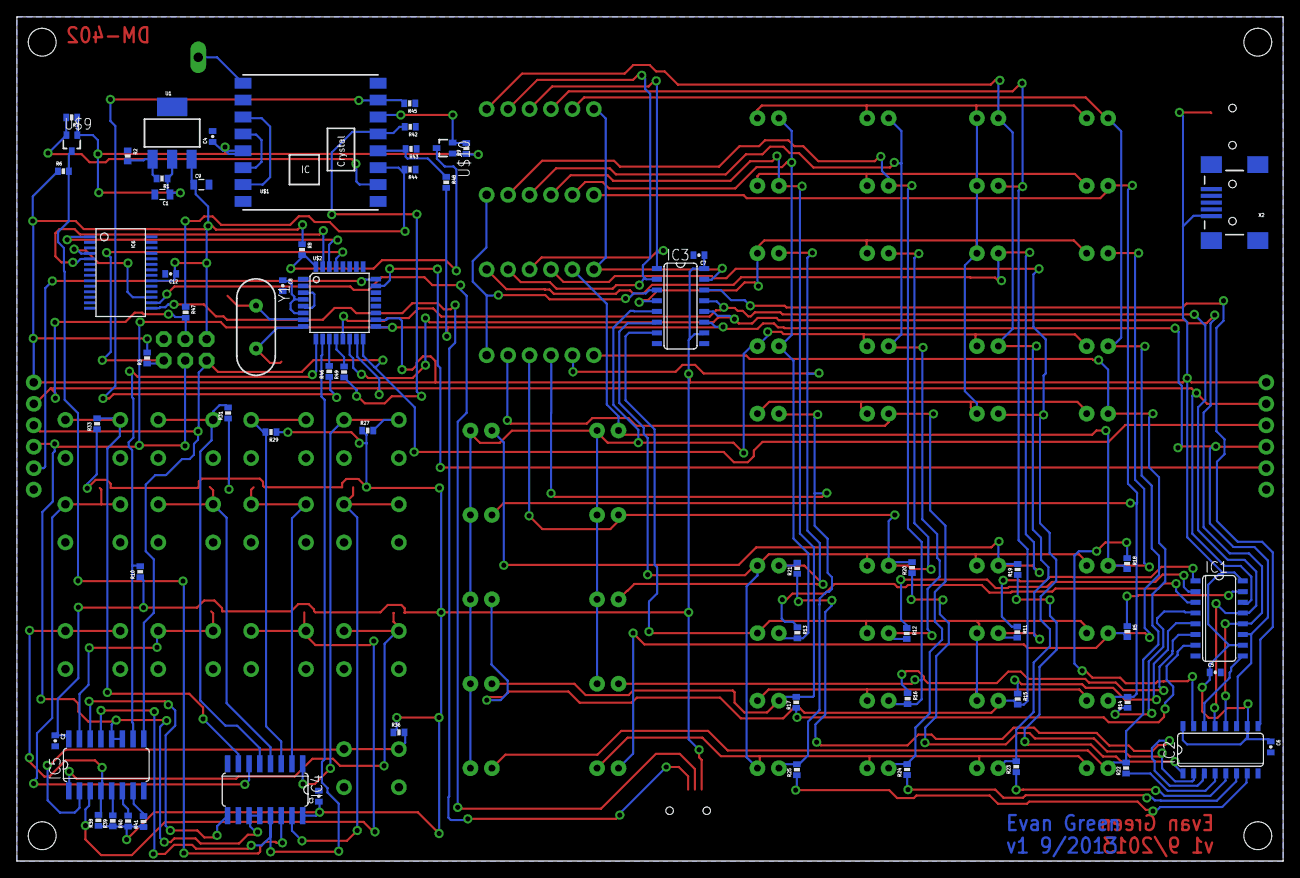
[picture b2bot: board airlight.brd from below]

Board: 2 copper layers, 150.0 x 100.0 mm, 144 parts (64 on the bottom side), 94 nets.

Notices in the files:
binyclock.c:
Copyright (c) 2011 Evan Green
usbled.c:
Copyright (C) 2006 Dick Streefland
Copyright (c) 2010 Evan Green
This is free software, licensed under the terms of the GNU General
parts and their libraries:
SparkFun: Licensing: CC v3.0 Share-Alike You are welcome to use this library for commercial purposes.
microbuilder: This work is placed in the public domain, and may be freely used for commercial and non-commercial work with the following conditions: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
